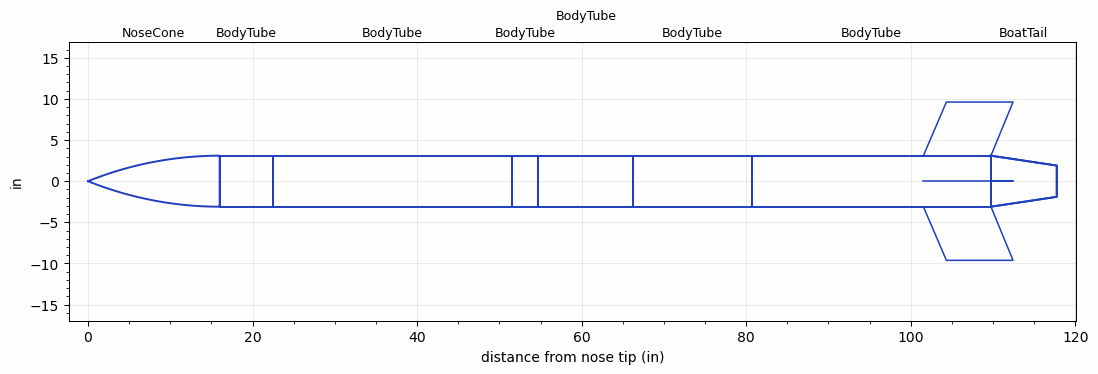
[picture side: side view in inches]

<RASAeroDocument>
 <FileVersion>2</FileVersion>
 <RocketDesign>
  <NoseCone>
   <Length>16</Length>
   <Diameter>6.2</Diameter>
   <Shape>Tangent Ogive</Shape>
   <Location>0</Location>
  </NoseCone>
  <BodyTube>
   <Length>6.5</Length>
   <Diameter>6.2</Diameter>
   <Location>16</Location>
  </BodyTube>
  <BodyTube>
   <Length>28.9999</Length>
   <Diameter>6.2</Diameter>
   <Location>22.5</Location>
   <Protuberance>
    <StreamlinedNoBaseDrag>0.38</StreamlinedNoBaseDrag>
    <StreamlinedWithBaseDrag>0</StreamlinedWithBaseDrag>
    <InclinedPlate1Angle>0</InclinedPlate1Angle>
    <InclinedPlate1FrontalArea>0</InclinedPlate1FrontalArea>
    <InclinedPlate2Angle>0</InclinedPlate2Angle>
    <InclinedPlate2FrontalArea>0</InclinedPlate2FrontalArea>
   </Protuberance>
  </BodyTube>
  <BodyTube>
   <Length>3.25</Length>
   <Diameter>6.2</Diameter>
   <Location>51.4999</Location>
  </BodyTube>
  <BodyTube>
   <Length>11.5</Length>
   <Diameter>6.2</Diameter>
   <Location>54.7499</Location>
   <Protuberance>
    <StreamlinedNoBaseDrag>0.38</StreamlinedNoBaseDrag>
    <StreamlinedWithBaseDrag>0</StreamlinedWithBaseDrag>
    <InclinedPlate1Angle>0</InclinedPlate1Angle>
    <InclinedPlate1FrontalArea>0</InclinedPlate1FrontalArea>
    <InclinedPlate2Angle>0</InclinedPlate2Angle>
    <InclinedPlate2FrontalArea>0</InclinedPlate2FrontalArea>
   </Protuberance>
  </BodyTube>
  <BodyTube>
   <Length>14.5</Length>
   <Diameter>6.2</Diameter>
   <Location>66.2499</Location>
  </BodyTube>
  <BodyTube>
   <Length>28.9999</Length>
   <Diameter>6.2</Diameter>
   <RailGuideDiameter>0.621</RailGuideDiameter>
   <RailGuideHeight>0.6845</RailGuideHeight>
   <Location>80.7499</Location>
   <BoattailLength>8</BoattailLength>
   <BoattailRearDiameter>3.8</BoattailRearDiameter>
   <Fin>
    <Count>4</Count>
    <Chord>8.213</Chord>
    <Span>6.52</Span>
    <SweepDistance>2.795</SweepDistance>
    <TipChord>8.1</TipChord>
    <Thickness>0.2</Thickness>
    <Location>8.213</Location>
    <AirfoilSection>Rounded</AirfoilSection>
   </Fin>
   <Protuberance>
    <StreamlinedNoBaseDrag>0.38</StreamlinedNoBaseDrag>
    <StreamlinedWithBaseDrag>0</StreamlinedWithBaseDrag>
    <InclinedPlate1Angle>0</InclinedPlate1Angle>
    <InclinedPlate1FrontalArea>0</InclinedPlate1FrontalArea>
    <InclinedPlate2Angle>0</InclinedPlate2Angle>
    <InclinedPlate2FrontalArea>0</InclinedPlate2FrontalArea>
   </Protuberance>
  </BodyTube>
  <BoatTail>
   <Length>8</Length>
   <Diameter>6.2</Diameter>
   <RearDiameter>3.8</RearDiameter>
   <Location>109.7498</Location>
  </BoatTail>
  <Surface>Sheet Metal</Surface>
  <ModifiedBarrowman>False</ModifiedBarrowman>
  <Turbulence>True</Turbulence>
  <UseBooster1>False</UseBooster1>
  <UseBooster2>False</UseBooster2>
 </RocketDesign>
 <LaunchSite>
  <Altitude>2870.735</Altitude>
  <Pressure>28.9828</Pressure>
  <RodAngle>6</RodAngle>
  <RodLength>163.9997</RodLength>
  <Temperature>86</Temperature>
  <WindSpeed>15</WindSpeed>
 </LaunchSite>
 <Recovery>
  <Altitude1>1499.344</Altitude1>
  <Altitude2>656.168</Altitude2>
  <DeviceType1>Parachute</DeviceType1>
  <DeviceType2>Parachute</DeviceType2>
  <Event1>True</Event1>
  <Event2>True</Event2>
  <Size1>95.9998</Size1>
  <Size2>35.9999</Size2>
  <EventType1>Altitude</EventType1>
  <EventType2>Apogee</EventType2>
  <CD1>1.35</CD1>
  <CD2>0</CD2>
 </Recovery>
 <SimulationList>
  <Simulation>
   <SustainerLaunchWt>61.4316</SustainerLaunchWt>
   <SustainerCG>68.586</SustainerCG>
   <SustainerIgnitionDelay>0</SustainerIgnitionDelay>
   <Booster1SeparationDelay>0</Booster1SeparationDelay>
   <Booster1IgnitionDelay>0</Booster1IgnitionDelay>
   <IncludeBooster1>False</IncludeBooster1>
   <Booster2Delay>0</Booster2Delay>
   <IncludeBooster2>False</IncludeBooster2>
  </Simulation>
 </SimulationList>
</RASAeroDocument>
